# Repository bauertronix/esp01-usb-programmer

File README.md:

![N|Solid](https://lh3.googleusercontent.com/m9MQOhnfOrxOZb1wryZ34_em63xyXnbdRx7WWmDhYnlRtX7pZSaB2tOT9EthOZ8ZP891h-4Sf2g7IS-1fqFYvFBhNpppph7J3Bpl1IDl_kuzQaX29F0UUmrvcLtGsjyk3lpeKdsOokL1Kq6bmfErdijxwTtSsXrugsPBAInUXFXLpR2pSTGHhk_w4q0h-JfaoIvZ_pnPNm8EfBCOXkrC1tY6gV3QYq-1SXIBwHaR6yglWE2Jwa7Akfg1uBLgPJs8Wn6lE4C_j6aeFCoaRaAI1R6gu9JAOE33orgHNhA5Q1jmAYRuAIGpv_2NmJnWOXkmTQc-8rxgUyHyMje6TrtOwgNXw5Wvst9IvTumkA3WXHfL7DO-JCjLvJGU85M-bdar0xF52RCpKeJmpIgnqA7GY6YZohbX5y3jTPcLEg0oImvQ-DpxpFCL3HTvv7zEBtXRn_6u5mv38eSqdHQavmLEseAA7Es2M_EdLiyKnKFFFYGOQ9RGkTP5OmrX0qI_zhDhk0iWN6memKXfbDpYIY3uMdk0Je3fAN1yhi49NJJL1vZMuIMaaM-YUJ0FpsbPaPIXfl5e4p4zpSap7UQMI3Z14GAdtLIBmlSY0fusEagwJHlE62mWLaWz3Zv-IhaXeiI=w403-h42-no)

# USB Programmer for ESP8266-01
Small, compact usb programmer for ESP8266-01. Open hardware project designed with KiCAD, assembled in Brazil.

![N|Solid](https://lh3.googleusercontent.com/T6-2Vr6gjXeOHPq4WVG8riyvhUr5bAIlzdpFoq4GWs9mi4zZqg3pyui8kG0gsxebRmTtDLGT0JklO9HM_JemkBkr81K5_HCM5yLjw04tj_nZ6GxwVn5-ilcCgj6oVff7qqQOCzxcc-1QtK1DBt_sIQ_2hP0xlhb3RqGGiXvpXXNNp-LYYJdEyJffZdIsXXLbcn6wBcwuh50TKaMnGKuRUw0BIkzQ8ajZjhf0wA7RCgrWxDx3KYtav0wiyzH2NdJkHzA7MmptHoMT2tzqooolcZYuhZkClsZiceBzoHx9G8d4UOscBBRhDhiLAB8mm50JwN5ykeCHxZC2WPMaAm4ScFF_F6i-9KxbJA_GQ4szfwU9fYVRp-6zzrFTAWN4Bug2gHxGLiG2DRqeq613CtB_T8EdP2HSSn_v4eh05HoNCr0HUEcRkwFvgLfgg3HPEFB9Flwq5jJfh1zRHDuGxFIermTuDx3woi5WLKVUd1s06f2FKivuj4gXEy3-EKC6oqvisYOjyf_R7o3D4XuH1ReNJ2GySPYI2TFJBVzKZDLG5PkFrPrdKM8xY0oMBeNiGhiEC7Phrm-qi9Ywd8_myr36Dgtht_l5WOBj0DyfBSCkVcDitynnUfwr2ou8PAmJ9gs=w850-h510-no)

## Schematics

![N|Solid](https://lh3.googleusercontent.com/pIMWJWW7bDx7-SM0VJmtOGuVBDfyxB3j-54ZM0__Vb6cUB0VIyKpyr1-qruGuSXM1p7nMTrriWeazPjMGI3eTuyR4UQTiGG7hKoZsgU84DFYYJhNZZknQgjnJuuikyBtLUnK4GjA6kEqyhwJ78696LwnKSMN3PiA6nxD4Qv7jp_PTHKmNgMTXA5QLSp0r0HZdT4QtpEfBIWPfhR9Vc7J6YG3uIqxhEsKHfBwSEk58ea5n-HsHU9bGF580llS2JGj_hGw7p2WYmrpGIZs8W9GzZ1syMSkEWcjbpGRBgY1qG3gExU_-vUUPceKoO2LGi-TW8DnUV690bZPe5UAgwYTRO0RA0E4z-0jfs_MLM2YQcyUjL1OyDJFfhCQoLR_abXktMhpH4NLaNi6WXkD1WRVmHcyfDMViij9cSATUvnkv8KmX5Z_3pDfB6LKlaJcGMvM6_7SKOEAAI5uIa6WamEq0zsl5sSWAU4nDXDMGoj5AWzT_CdlYQ1ewUNo1B0LciW1w1r0N1e9J2WGDEWDd0iHTJIDXARajb8pp8evKEqk-3GudzEgUBwF6_9LuIOKmBU3l0I3JB05NmU50akus7LJNNCMMkoQuya3c4c3-QLGxYHOWt8IhL_qbriB7KAcDO0=w1694-h883-no)

## See it in action!

[![N|Solid](https://lh3.googleusercontent.com/BAYfgDBrj4tj6n1qpRZ1H5OQVTh9z1QqO-qSwmZVvk1hDeqzWiCUNfmsG8Zp4ZUL4SuYPdpLMjgkyfe-SD4mew7cMUS_Km4z5qDh192PwlLtZ7lbMwpLinAAf7JDLQ19xpJFgCNB-_0MJDxJQD2VEhDnHc6UrKBLt2uNvZ2sM6jlsCKrCE69o7PuCHC2dWd0dxfQxbqJuKVZ1oYVHl4rzxWokqYwXdwFpMZPczxcp56m0Bkr9t8r7_SROyXJltw23_SCIUMCyldlzw2Tn2rWFb4lDHN7dRXfauKLkYz2L_QX8Gg88x-fxuiQ6QQ5f32cgpvdiKnmQ-vAU6CpvZKYCL8vvrwsCtHMGL6377KrsmKWlHLUSjTBGv_OfjjFbtwmqPXnGJHDkdp_fUX40axOpFBA6PmnpJ2p3xzXao3FZcJa4PdEmnjibdArLKG1WFCAEJ5bBInpqHCrgO9t327sI7NHJkoejkvA0ZwaZl1HoK90nqNUYBF761rcwU_T3EmDMtEKfOwHUUFEUeySMXDiaEtqpW7ki-xu7fKpCmHAGGqs8Ky2FAqZeXmeAogi6wBtcosJh0p4-Ix7ikcwj37h8oseH4QCPdvk0NE0oDpDzql8io6DXQX5Hv99mKnIR9c=w615-h346-no)](https://www.youtube.com/watch?v=P84HuPpxpRY)

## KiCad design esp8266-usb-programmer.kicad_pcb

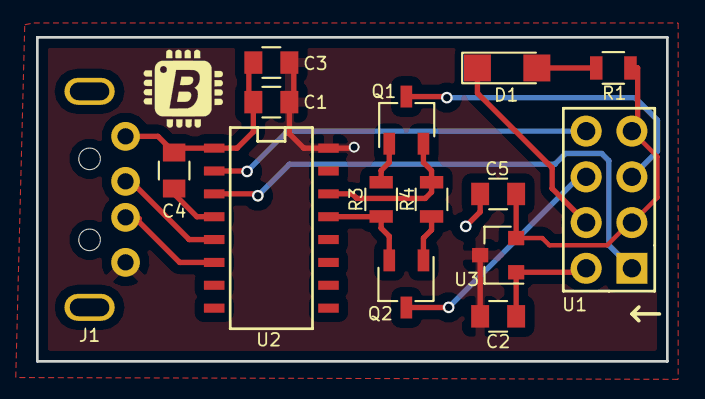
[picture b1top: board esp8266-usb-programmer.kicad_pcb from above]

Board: 2 copper layers, 35.0 x 18.0 mm, 15 parts (0 on the bottom side), 16 nets.

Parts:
C1, C2, C5: 2.2uF; C_0805
C3: 100nF; C_0805
C4: 10nF; C_0805
D1: D1; LED_1206
J1: USB_A; USB_A_PCB
Q1, Q2: S8050-SOT23; TSOT-23
R1: 1K; R_0805
R3, R4: 12K; R_0805
U1: ESP-01v090; ESP-01
U2: CH340C; SO-16-N
U3: 662K LDO SOT23; SOT-23

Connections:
+3V3: C5.1, R1.2, U1.3, U1.7, U3.2
+5V: C1.1, C2.1, C3.1, J1.1, U2.16, U3.3
/D+: J1.3, U2.5
/D-: J1.2, U2.6
/DTR: Q2.2, R3.1, U2.13
/ESP_RX: U1.8, U2.2
/ESP_TX: U1.1, U2.3
/GPIO0: Q2.3, U1.6
/RESET: Q1.3, U1.5
/RTS: Q1.2, R4.1, U2.14
GND: C1.2, C2.2, C3.2, C4.2, C5.2, J1.4, J1.5, U1.2, U2.1, U3.1
unnamed: C4.1, U2.4
unnamed: D1.1, U1.4
unnamed: D1.2, R1.1
unnamed: Q1.1, R3.2
unnamed: Q2.1, R4.2

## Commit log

2018-10-12 add project
2018-10-14 Create LICENSE
